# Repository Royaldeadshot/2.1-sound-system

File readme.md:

# DIY 3-Way Speaker Crossover + Amplifier System

This project is a custom-built 3-way audio system designed from scratch, including the amplifier, crossover network, and speaker configuration. The goal was to create a solid, practical setup that delivers good sound without overcomplicating the design.

---

## 🔊 System Overview

- Subwoofer: 10" DVC (handles low frequencies)
- Tower Speakers (x2):
  - 2 × Woofers (connected in series → 8Ω)
  - 1 × Midrange driver (4Ω)
  - 1 × Tweeter (4Ω)

- Passive 3-way crossover (2nd order)
- Custom PCB amplifier
  - Dual TPA3255 based amplifier

---

## 📸 Screenshots

### Full Build

### PCB Layout

---

### Schematic

---

### 3D Model

---

### Crossover Design

---

## ⚙️ How It Works (Short)

The Power supply power up the sytem and then 48V and 12V are sent to amp power pins, and then 12v is also used to power up the fans for cooling the HOT TPA3255 chips, then the 5v is sent to bt module

after that we select aux or bt input through the dpdt switch, and the signal goes to the tower amp and a 80hz cutoff is sent to the sub amp, the amp amplify the dignal and then the amplifier sends a full-range audio signal to the crossover in tower speaker and the cutoff freq to sub.

The crossover splits this signal into three parts:

- Low frequencies → go to the woofers  
- Mid frequencies → go to the mid driver  
- High frequencies → go to the tweeter  

This is done using inductors and capacitors arranged as filters:

- Inductors block high frequencies  
- Capacitors block low frequencies  

Each driver only receives the frequencies it is meant to play, improving clarity and reducing distortion.

---

## 🧠 Design Choices

- TPA3255 for 250 watt per channel and 300-600 Watt for sub
- Used a 2nd order crossover (12dB/octave) for better separation   
- used a active crossover for sub to save cost

---

## 🧾 Components Used

BOM list present in the bom.csv in this repo root directory

---

## 🚀 Status

- [x] Amplifier designed  
- [x] PCB layout completed  
- [x] Crossover designed
- [X] Input Stage made
- [X] SUB frequecny cutoff of 80hz made
- [X] Tuned Enclosure design made
- [X] Drivers selected
- [X] BOM made
- [ ] Assembly  
- [ ] Testing  

---

## 📌 Future Improvements

- Fine-tune crossover after listening tests  
- Improve enclosure design  
- Add damping and internal bracing  

---

This is a work-in-progress build focused on learning and practical implementation rather than perfection.

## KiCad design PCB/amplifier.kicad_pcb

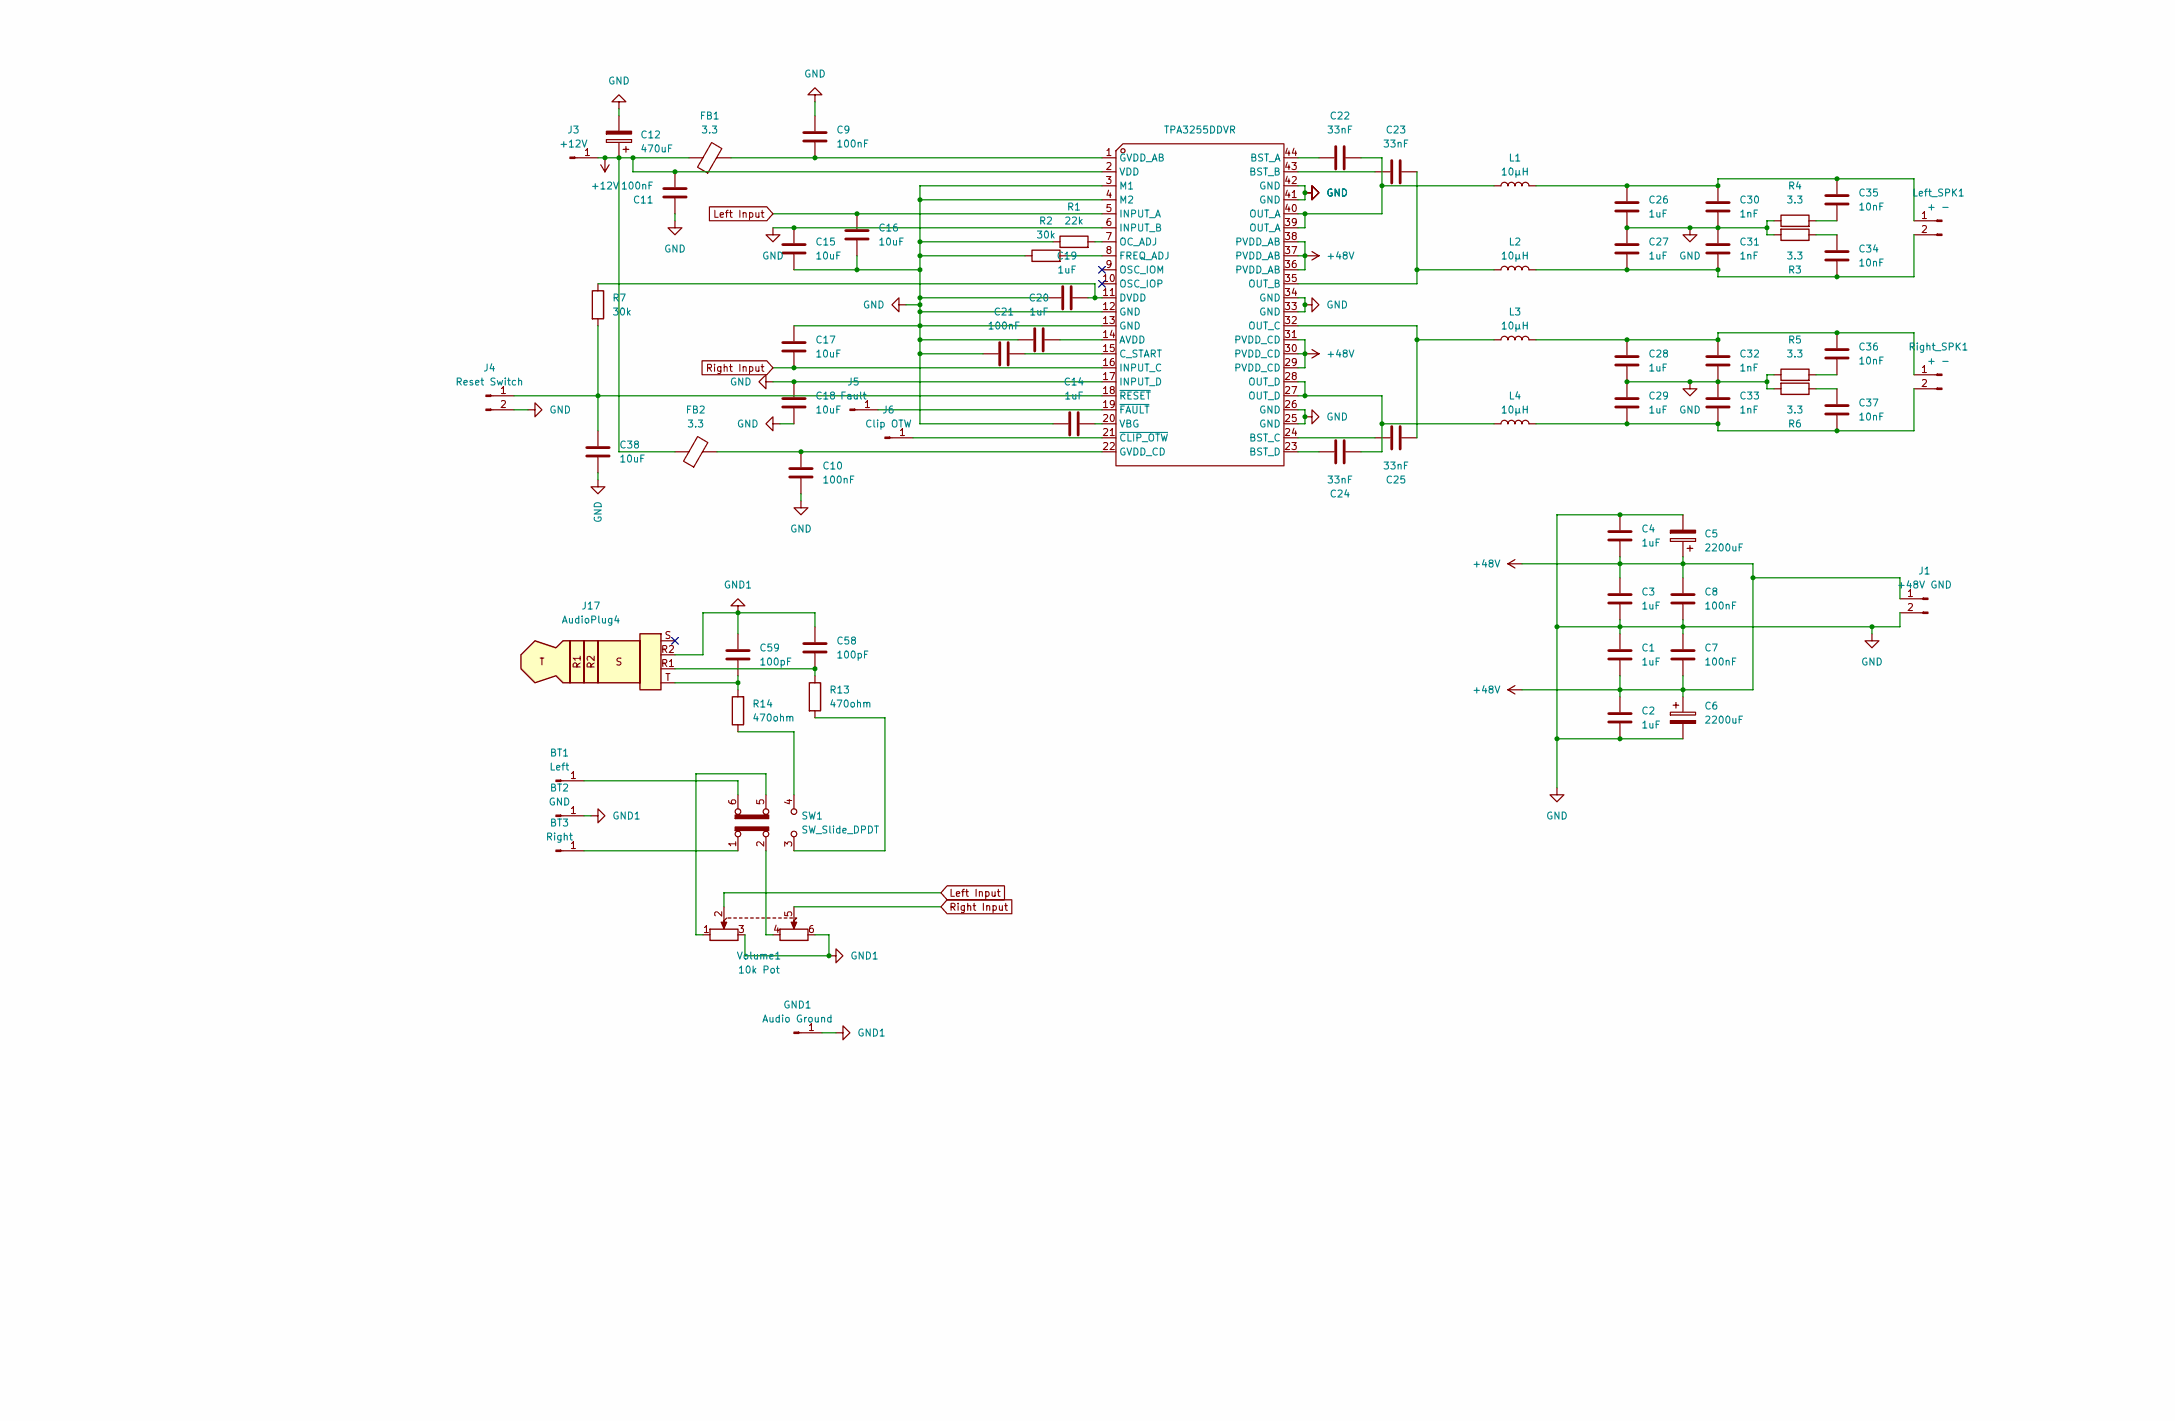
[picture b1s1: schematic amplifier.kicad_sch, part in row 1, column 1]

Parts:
BT1: Left; SolderWirePad_1x01_SMD_2x4mm
BT2: GND; SolderWirePad_1x01_SMD_2x4mm
BT3: Right; SolderWirePad_1x01_SMD_2x4mm
C1, C2, C3, C4, C26, C27, C28, C29: 1uF; C_1210_3225Metric_Pad1.33x2.70mm_HandSolder
C5, C6: 2200uF; CP_Radial_D18.0mm_P7.50mm
C7, C8, C9, C10, C11, C21: 100nF; C_0805_2012Metric_Pad1.18x1.45mm_HandSolder
C12: 470uF; CP_Radial_D10.0mm_P5.00mm
C14, C19, C20: 1uF; C_0603_1608Metric_Pad1.08x0.95mm_HandSolder
C15, C16, C17, C18, C38: 10uF; C_0805_2012Metric_Pad1.18x1.45mm_HandSolder
C22, C23, C24, C25: 33nF; C_1206_3216Metric_Pad1.33x1.80mm_HandSolder
C30, C31, C32, C33: 1nF; C_0805_2012Metric_Pad1.18x1.45mm_HandSolder
C34, C35, C36, C37: 10nF; C_0805_2012Metric_Pad1.18x1.45mm_HandSolder
C58, C59: 100pF; C_Disc_D5.0mm_W2.5mm_P2.50mm
FB1, FB2: 3.3; R_1206_3216Metric_Pad1.30x1.75mm_HandSolder
GND1: Audio Ground; SolderWirePad_1x01_SMD_4x8mm
J1: +48V GND; TerminalBlock_Phoenix_MKDS-1,5-2_1x02_P5.00mm_Horizontal
J3: +12V; SolderWirePad_1x01_SMD_4x8mm
J4: Reset Switch; PinHeader_1x02_P1.00mm_Vertical
J5: Fault; SolderWirePad_1x01_SMD_3x6mm
J6: Clip OTW; SolderWirePad_1x01_SMD_3x6mm
J17: AudioPlug4; Plug_3.5mm_CUI_SP-3541
L1, L2, L3, L4: 10µH; L_APV_APH1265
Left_SPK1: + -; TerminalBlock_Phoenix_MKDS-1,5-2_1x02_P5.00mm_Horizontal
R1: 22k; R_Axial_DIN0207_L6.3mm_D2.5mm_P7.62mm_Horizontal
R2, R7: 30k; R_Axial_DIN0207_L6.3mm_D2.5mm_P10.16mm_Horizontal
R3, R4, R5, R6: 3.3; R_1206_3216Metric_Pad1.30x1.75mm_HandSolder
R13, R14: 470ohm; R_Axial_DIN0411_L9.9mm_D3.6mm_P12.70mm_Horizontal
Right_SPK1: + -; TerminalBlock_Phoenix_MKDS-1,5-2_1x02_P5.00mm_Horizontal
SW1: SW_Slide_DPDT; SW_CK_JS202011AQN_DPDT_Angled
U1: TPA3255DDVR; HTSSOP-44_L14.0-W6.1-P0.64-LS8.1-BL; LCSC Part C468240
Volume1: 10k Pot; Potentiometer_Alpha_RD902F-40-00D_Dual_Vertical

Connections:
+12V: C11.2, C12.1, FB1.1, FB2.1, J3.1, U1.2 (VDD); also elsewhere on the board
+48V: C1.2, C2.1, C3.1, C4.2, C5.1, C6.1, C7.2, C8.1, J1.1, U1.29 (PVDD_CD), U1.30 (PVDD_CD), U1.31 (PVDD_CD), U1.36 (PVDD_AB), U1.37 (PVDD_AB), U1.38 (PVDD_AB); also elsewhere on the board
GND: C1.1, C2.2, C3.2, C4.1, C5.2, C6.2, C7.1, C8.2, C9.2, C10.1, C11.1, C12.2, C14.2, C15.1, C15.2, C16.2, C17.1, C18.1, C18.2, C19.1, C20.1, C21.1, C26.2, C27.1, C28.2, C29.1, C30.2, C31.1, C32.2, C33.1, C38.1, J1.2, J4.2, R1.1, R2.1, R3.2, R4.1, R5.1, R6.2, U1.3 (M1), U1.4 (M2), U1.6 (INPUT_B), U1.12 (GND), U1.13 (GND), U1.17 (INPUT_D), U1.25 (GND), U1.26 (GND), U1.33 (GND), U1.34 (GND), U1.41 (GND), U1.42 (GND); also elsewhere on the board
GND1: BT2.1, C58.1, C59.2, GND1.1, J17.R2, Volume1.3, Volume1.6; also elsewhere on the board
Left Input: C16.1, U1.5 (INPUT_A), Volume1.2; also elsewhere on the board
unnamed: BT1.1, SW1.6 (C)
unnamed: BT3.1, SW1.1 (A)
unnamed: C22.2, L1.1, U1.39 (OUT_A), U1.40 (OUT_A)
unnamed: C24.1, L4.1, U1.27 (OUT_D), U1.28 (OUT_D)
unnamed: C34.1, R3.1
unnamed: C35.2, R4.2
unnamed: C36.2, R5.2
unnamed: C37.1, R6.1
unnamed: C58.2, J17.R1, R13.1
unnamed: C59.1, J17.T, R14.2
unnamed: C38.2, J4.1, R7.2, U1.18 (~RESET)
unnamed: J5.1, U1.19 (~FAULT)
unnamed: J6.1, U1.21 (~CLIP_OTW)
unnamed: C26.1, C30.1, C35.1, L1.2, Left_SPK1.1
unnamed: C27.2, C31.2, C34.2, L2.2, Left_SPK1.2
unnamed: R13.2, SW1.3 (C)
unnamed: R14.1, SW1.4 (A)
unnamed: C28.1, C32.1, C36.1, L3.2, Right_SPK1.1
unnamed: C29.2, C33.2, C37.2, L4.2, Right_SPK1.2
unnamed: SW1.2 (B), Volume1.4
unnamed: SW1.5 (B), Volume1.1
unnamed: C20.2, U1.14 (AVDD)
unnamed: C22.1, U1.44 (BST_A)
unnamed: C23.1, U1.43 (BST_B)
unnamed: C25.2, U1.24 (BST_C)
unnamed: C24.2, U1.23 (BST_D)
unnamed: C21.2, U1.15 (C_START)
unnamed: C19.2, R7.1, U1.11 (DVDD)
unnamed: R2.2, U1.8 (FREQ_ADJ)
unnamed: C9.1, FB1.2, U1.1 (GVDD_AB)
unnamed: C10.2, FB2.2, U1.22 (GVDD_CD)
unnamed: R1.2, U1.7 (OC_ADJ)
unnamed: C23.2, L2.1, U1.35 (OUT_B)
unnamed: C25.1, L3.1, U1.32 (OUT_C)
unnamed: C14.1, U1.20 (VBG)
Right Input: C17.2, U1.16 (INPUT_C), Volume1.5; also elsewhere on the board

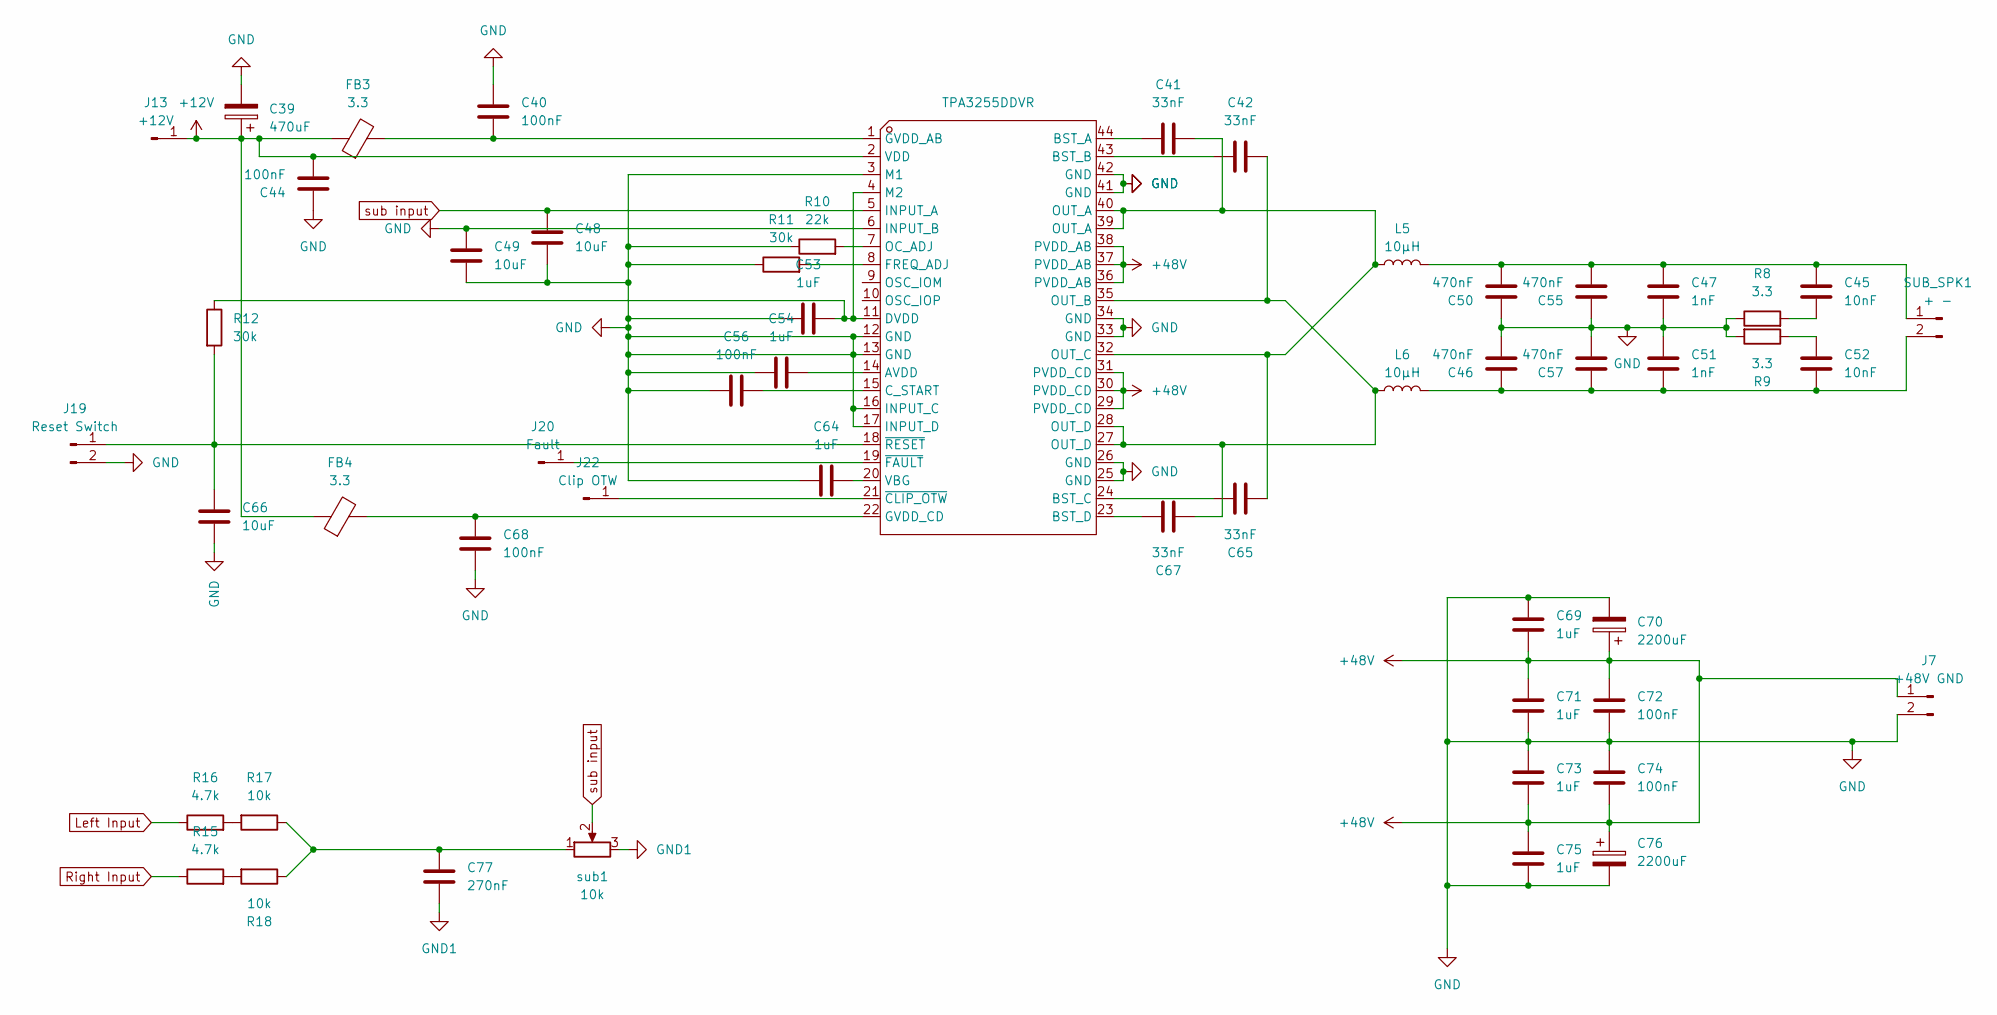
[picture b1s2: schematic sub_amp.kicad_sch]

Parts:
C39: 470uF; CP_Radial_D10.0mm_P5.00mm
C40, C44, C56, C68, C72, C74: 100nF; C_0805_2012Metric_Pad1.18x1.45mm_HandSolder
C41, C42, C65, C67: 33nF; C_1206_3216Metric_Pad1.33x1.80mm_HandSolder
C45, C52: 10nF; C_0805_2012Metric_Pad1.18x1.45mm_HandSolder
C46, C50, C55, C57: 470nF; C_1206_3216Metric_Pad1.33x1.80mm_HandSolder
C47, C51: 1nF; C_0805_2012Metric_Pad1.18x1.45mm_HandSolder
C48, C49, C66: 10uF; C_0805_2012Metric_Pad1.18x1.45mm_HandSolder
C53, C54, C64: 1uF; C_0603_1608Metric_Pad1.08x0.95mm_HandSolder
C69, C71, C73, C75: 1uF; C_1210_3225Metric_Pad1.33x2.70mm_HandSolder
C70, C76: 2200uF; CP_Radial_D18.0mm_P7.50mm
C77: 270nF; C_0805_2012Metric_Pad1.18x1.45mm_HandSolder
FB3, FB4: 3.3; R_1206_3216Metric_Pad1.30x1.75mm_HandSolder
J7: +48V GND; TerminalBlock_Phoenix_MKDS-1,5-2_1x02_P5.00mm_Horizontal
J13: +12V; SolderWirePad_1x01_SMD_4x8mm
J19: Reset Switch; PinHeader_1x02_P1.00mm_Vertical
J20: Fault; SolderWirePad_1x01_SMD_3x6mm
J22: Clip OTW; SolderWirePad_1x01_SMD_3x6mm
L5, L6: 10µH; L_APV_APH1265
R8, R9: 3.3; R_1206_3216Metric_Pad1.30x1.75mm_HandSolder
R10: 22k; R_Axial_DIN0207_L6.3mm_D2.5mm_P7.62mm_Horizontal
R11, R12: 30k; R_Axial_DIN0207_L6.3mm_D2.5mm_P10.16mm_Horizontal
R15, R16: 4.7k; R_Axial_DIN0411_L9.9mm_D3.6mm_P12.70mm_Horizontal
R17, R18: 10k; R_Axial_DIN0207_L6.3mm_D2.5mm_P7.62mm_Horizontal
SUB_SPK1: + -; TerminalBlock_Phoenix_MKDS-1,5-2_1x02_P5.00mm_Horizontal
U2: TPA3255DDVR; HTSSOP-44_L14.0-W6.1-P0.64-LS8.1-BL; LCSC Part C468240
sub1: 10k; Potentiometer_ACP_CA6-H2,5_Horizontal

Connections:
+12V: C39.1, C44.2, FB3.1, FB4.1, J13.1, U2.2 (VDD); also elsewhere on the board
+48V: C69.2, C70.1, C71.1, C72.1, C73.2, C74.2, C75.1, C76.1, J7.1, U2.29 (PVDD_CD), U2.30 (PVDD_CD), U2.31 (PVDD_CD), U2.36 (PVDD_AB), U2.37 (PVDD_AB), U2.38 (PVDD_AB); also elsewhere on the board
GND: C39.2, C40.2, C44.1, C46.2, C47.2, C48.2, C49.1, C49.2, C50.1, C51.1, C53.1, C54.1, C55.1, C56.1, C57.2, C64.2, C66.1, C68.1, C69.1, C70.2, C71.2, C72.2, C73.1, C74.1, C75.2, C76.2, J7.2, J19.2, R8.1, R9.2, R10.1, R11.1, U2.3 (M1), U2.6 (INPUT_B), U2.12 (GND), U2.13 (GND), U2.16 (INPUT_C), U2.17 (INPUT_D), U2.25 (GND), U2.26 (GND), U2.33 (GND), U2.34 (GND), U2.41 (GND), U2.42 (GND); also elsewhere on the board
GND1: C77.2, sub1.3; also elsewhere on the board
Left Input: R16.1; also elsewhere on the board
unnamed: C45.2, R8.2
unnamed: C52.1, R9.1
unnamed: C77.1, R17.1, R18.1, sub1.1
unnamed: C66.2, J19.1, R12.2, U2.18 (~RESET)
unnamed: J20.1, U2.19 (~FAULT)
unnamed: J22.1, U2.21 (~CLIP_OTW)
unnamed: R15.2, R18.2
unnamed: R16.2, R17.2
unnamed: C45.1, C47.1, C50.2, C55.2, L5.2, SUB_SPK1.1
unnamed: C46.1, C51.2, C52.2, C57.1, L6.2, SUB_SPK1.2
unnamed: C54.2, U2.14 (AVDD)
unnamed: C41.1, U2.44 (BST_A)
unnamed: C42.1, U2.43 (BST_B)
unnamed: C65.2, U2.24 (BST_C)
unnamed: C67.2, U2.23 (BST_D)
unnamed: C56.2, U2.15 (C_START)
unnamed: C53.2, R12.1, U2.4 (M2), U2.11 (DVDD)
unnamed: R11.2, U2.8 (FREQ_ADJ)
unnamed: C40.1, FB3.2, U2.1 (GVDD_AB)
unnamed: C68.2, FB4.2, U2.22 (GVDD_CD)
unnamed: R10.2, U2.7 (OC_ADJ)
unnamed: C42.2, C67.1, L6.1, U2.27 (OUT_D), U2.28 (OUT_D), U2.35 (OUT_B)
unnamed: C41.2, C65.1, L5.1, U2.32 (OUT_C), U2.39 (OUT_A), U2.40 (OUT_A)
unnamed: C64.1, U2.20 (VBG)
Right Input: R15.1; also elsewhere on the board
sub input: C48.1, U2.5 (INPUT_A), sub1.2

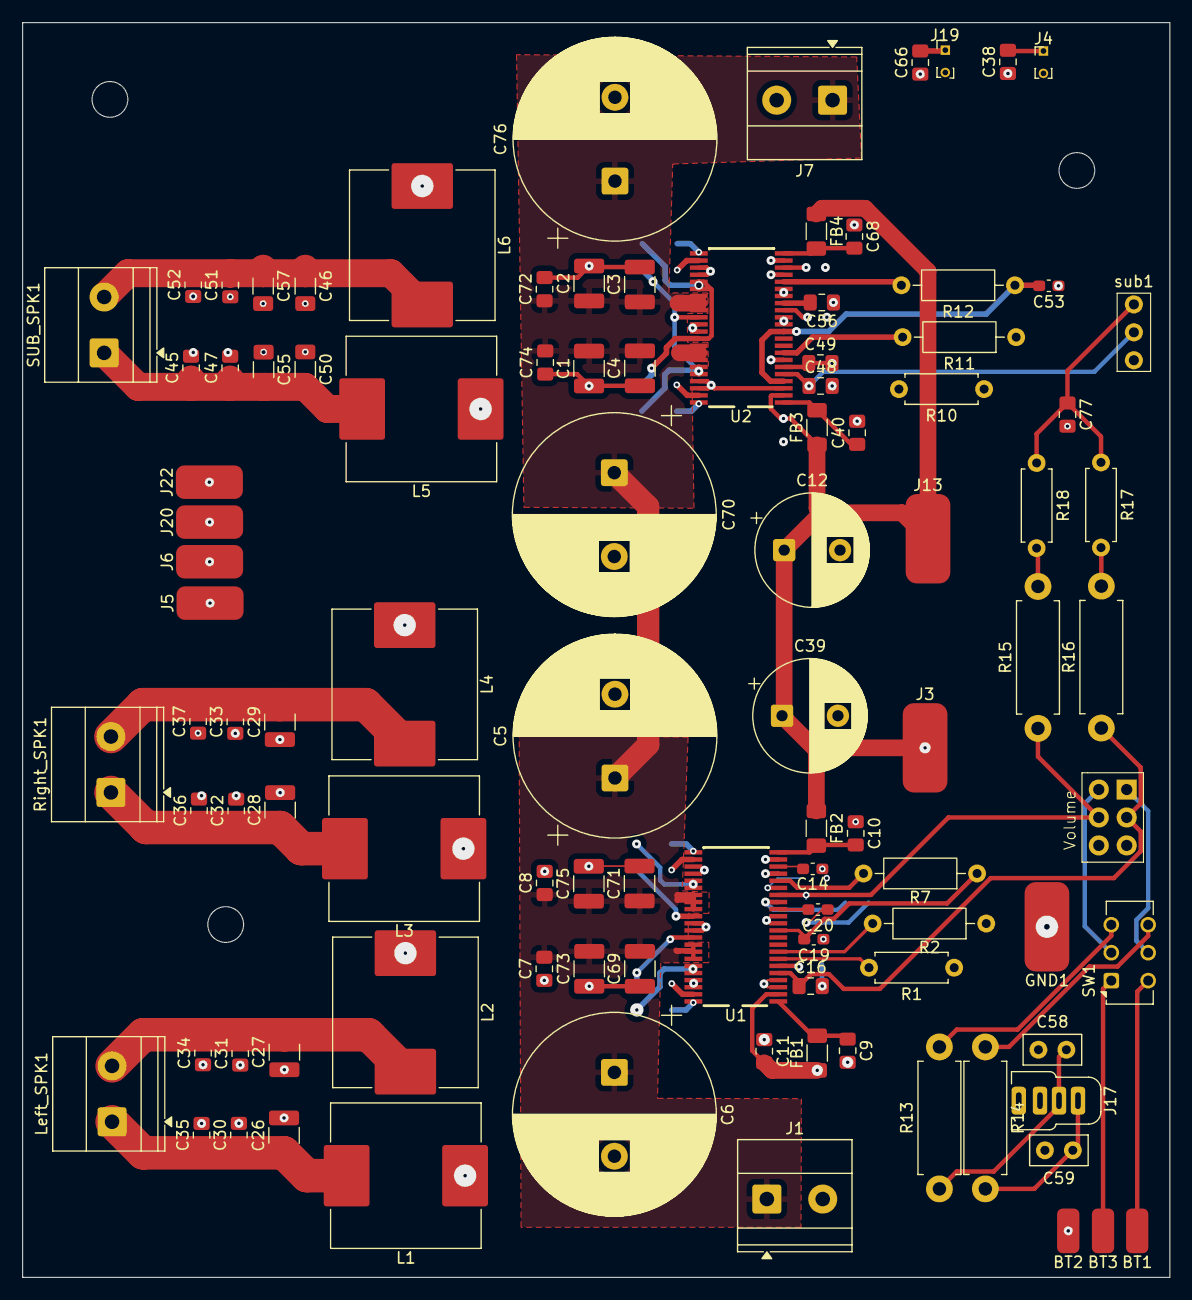
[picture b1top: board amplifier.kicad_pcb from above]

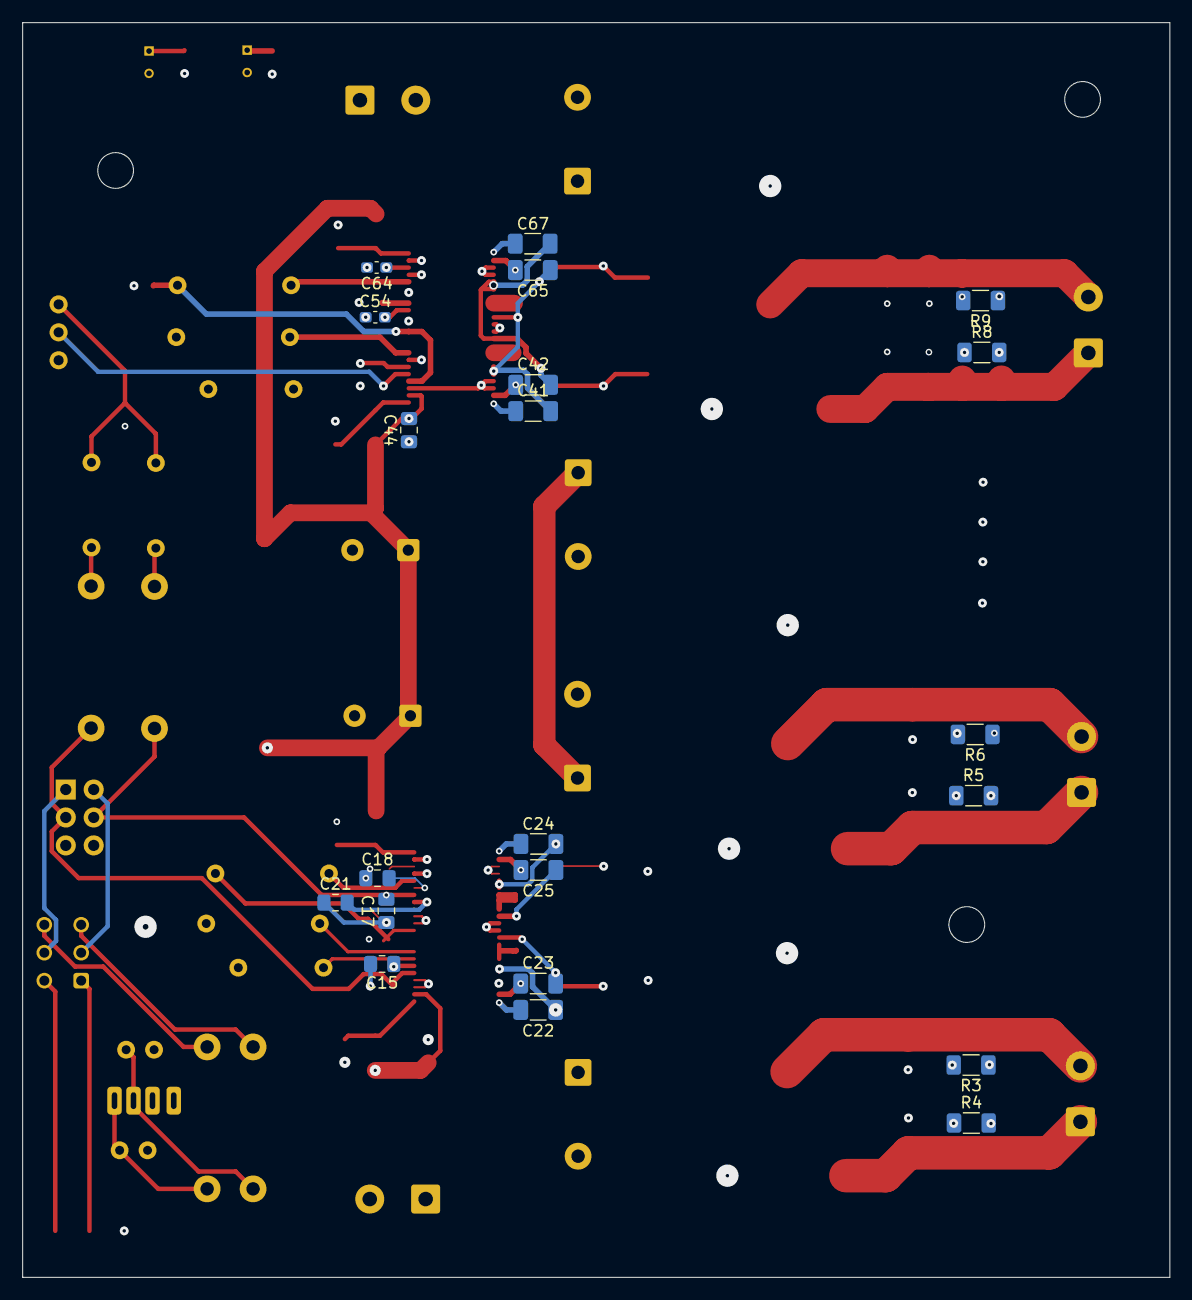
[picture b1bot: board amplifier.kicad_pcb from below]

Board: 4 copper layers, 102.7 x 112.3 mm, 122 parts (21 on the bottom side), 66 nets.

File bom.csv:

S. No.,PCB Annotations,Part Name,Qty.,Unit Price(?),Total Price(?),Product link,LCSC Part No.
1,"U1,U2",TPA3255DDVR,2,396,807,https://www.lcsc.com/product-detail/C468240.html?s_z=n_tpa3255,C468240
2,L1-L6,10uH Inductor,7,32.5,276.6,https://www.lcsc.com/product-detail/C5349630.html,C5349630
3,SW1,DPDT switch,1,9,9,https://robu.in/product/sk-3245d-02-l4-xkb-50ma-dpdt-12v-12v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,
4,J17,aux input jack,1,2.75,2.75,https://robu.in/product/smartelex-audio-jack-3-5mm-trrs-smd/,
5,C77,270nF Ceramic Capacitor X7R 50V,2,0.64,1.28,https://robu.in/product/tcc0805x7r274k500dt-cctc-smt-ceramic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,
6,"C59,C58",100pF ceramic capacitor 50V,3,0.71,2.13,https://robu.in/product/100pf-50v-ceramic-capacitordip-pack-of-50/,
7,"R13,R14",470ohm resistor,3,1,3,https://robu.in/product/470-ohm-0-5w-metal-film-resistor-pac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,
8,J18,Bluetooth Module,1,300,300,https://robocraze.com/products/dfrobot-bluetooth-5-0-audio-r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,
9,SUB1,10k Potentiometer A taper,1,18,18,https://makerbazar.in/products/wh148-3pin-20mm-rotary-shaft-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,
10,VOLUME1,10k Potentiometer Dual gang,1,22,22,https://robu.in/product/10k%cf%89-0-2w-6-pin-2-gang-rotary-c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,
11,"R15,R16",4.7k ohm metal film resistor ,3,0.7,2.1,https://robu.in/product/4-7k-ohm-0-5w-metal-film-resistor-pa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,
12,"R17,R18",10k ohm metal film resistor,3,0.35,1.05,https://robu.in/product/10k-ohm-0-25w-metal-film-resistor-pa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,
13,"C1-4,C26-29,C69,C71,C73,C75",1uF Capacitor 100V ceramic,15,9,135,https://robu.in/product/cl32b105kcjnnne-samsang-100v-1uf-x7r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,
14,"C53,C54,C64,C19,C20,C14",1uF Capacitor 25V ceramic,8,1.61,12.88,https://robu.in/product/tmk107b7105ka-t-taiyo-yuden-mlcc-cap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,
15,"C5-6,C70,C76",2200uF electrolytic capacitor 63V,5,141,705,https://robu.in/product/upw1j222mhd-nichicon-2200uf-63v-%c2%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,
16,"C40,C44,C68,C56,C72,C74,C9-11,C21,C7-8",100nF ceramic capacitor,15,0.98,14.7,https://robu.in/product/cl21b104kcfnnwe-samsang-100v-100nf-x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,
17,"C12,C39",470uF Electrolytic capacitor 50V,3,7,21,https://robu.in/product/470uf-50v-through-hole-1020-electrol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,
18,"C15-18,C38,C48,C49,C66",10uF Ceramic Capacitor,10,3.17,31.7,https://robu.in/product/10uf-10000nf-25-v-capacitor-0805-smd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,
19,"C22-25,C41,C42,C65,C67",33nF 100V Ceramic Capacitor X7R,10,0.79,7.9,https://robu.in/product/tcc1206x7r333k101dt-cctc-smt-ceramic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,
20,"R1,R10",22k Ohm 0.25W Metal Film Resistor,4,0.25,1,https://robu.in/product/22k-ohm-0-25w-metal-film-resistor-pa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,
21,"R2,R7,R11,R12",30k Ohm metal film Resistor,5,2.18,10.9,https://robu.in/product/mf25-30k-multicomp-pro-through-hole-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,
22,"FB1-4, R3-R6,R8,R9",3.3Ohm Thick Filmc Resistor SMD,15,0.26,3.9,https://robu.in/product/1206w4f330kt5e-uniohm-royal-ohm-250m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,
23,"C30-C33, C47, C51",1nF Capacitor 100V,10,1.01,10.1,https://robu.in/product/cc0805krx7r0bb102-yageo-100v-1nf-x7r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,
24,"C34-C37, C45, C52",10nF Capacitor 100V ,10,1.79,17.9,https://robu.in/product/gcm21br72a103ka37l-murata-electronic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,
25,"C46, C50, C55, C57",470nF Capacitor 100V,6,1.73,10.38,https://robu.in/product/1206b474k101nt-fh-100v-470nf-x7r%c2%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,
26,,470nF Capacitor 100V,8,13,104,https://robu.in/product/xy104-5-0-xinya-2-pin-screw-terminal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,
27,,4mm Banana Plug Socket,8,13,104,https://robu.in/product/4mm-banana-socket-binding-post-nut-b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,
28,,48V To 12V Converter,1,128,128,https://robu.in/product/dc13-100v-to-12v-2a-buck-power-conve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,
29,,40mm Fan,2,65,130,https://makerbazar.in/products/generic-axial-dc-cooling-fan-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,
30,,Aluminium Heat Sink 9 x 9 x 12 mm,4,29,116,https://robocraze.com/products/aluminum-cooling-heat-sink-ch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,
31,,12V to 5V Converter,1,166,166,https://robu.in/product/24v-12v-to-5v-5a-power-module-dc-dc-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,
32,,Heat Shrink Sleeve 8mm,2,9,18,https://robu.in/product/heat-shrink-sleeve-8mm-black-industr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,
33,,48V Power Supply 1000 Watts,1,6999,6999,https://www.amazon.in/Switching-Universal-Regulated-Transfor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,
34,,39uF Capacitor for Crossover,2,13,26,https://robu.in/product/100yxg39mefc8x16-rubycon-39uf-100v-%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,
35,,68uF Capacitor for Crossover,2,18,36,https://robu.in/product/uhe2a680mpd1td-nichicon-68uf-%c2%b12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,
36,,2.5mH 16 AWG Steel Laminate Inductors,2,700,1400,https://audiofy.in/collections/air-core-coils/products/audio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,
37,,1.2mH 16 AWG Air Core Crossover Inductor,2,960,1920,https://audiofy.in/collections/air-core-coils/products/audio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,
38,,0.21mH 16 AWG Air Core Crossover Inductor,4,400,1600,https://audiofy.in/products/audiofy-0-21mh-16-awg-air-core-c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,
39,,6.8uF 400VDC Metalized Polypropylene Capacitor,2,190,380,https://audiofy.in/collections/capacitors/products/audiofy-6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,
40,,10uF 400VDC Metalized Polypropylene Capacitor,2,250,500,https://audiofy.in/collections/capacitors/products/audiofy-1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,
,,Acoustic Foam,1,1375,1375,https://www.amazon.in/gp/product/B0FYQCMLZ9/ref=ox_sc_act_ti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,
,,16AWG black wire,4,48,192,https://robu.in/product/16awg-high-voltage-silicone-wire-300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,
,,16AWG red wire,4,48,192,https://robu.in/product/16awg-high-voltage-silicone-wire-3000v-red/,
,,Multicore wire 14AWG,2,202,404,https://robu.in/product/14awg-multicore-insulated-cable2-cor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,
,,24AWG wire black,,12,12,https://robu.in/product/24awg-high-voltage-silicone-wire-300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,
,,24AWG wire red,,12,12,https://robu.in/product/24awg-high-voltage-silicone-wire-3000v-red/,
,,,,,,,
,,"Woofer 80W rms, 4ohm",4,489,1956,https://www.amazon.in/gp/product/B0GM8CFPC8/ref=ox_sc_act_ti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,
,,"Sub Woofer 450W rms , 4ohm, 10Inch",1,1749,1749,https://www.fredo.in/10-inch-DVC-Double-magnet-subwoofer,
,,"Mid Range Driver, 55W rms, 4ohm",2,700,1400,https://www.amazon.in/gp/product/B0DMVNY3SN/ref=ox_sc_act_ti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,
,,"Tweeter 15W rms, 4ohm pair",1,425,425,https://www.amazon.in/gp/product/B0F1N9MBHK/ref=ox_sc_act_ti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,
,,,,,,,
,,,,,,,
,,,,,,,
,,,,,,,
,,,,,,,
,,,,,,,
,,,,,,,
,,Wooden Enclosure,1,10000,Fulfilled by me,"sourced from local carpenter, Paid by me",

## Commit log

2026-03-25 pushhhhh
2026-03-25 photossss yah.
